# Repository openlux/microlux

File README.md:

This project is still in development.

# microlux

microlux is an open source design for an astrophotography autoguiding camera designed around the Aptina AR0130 image sensor.

### Hardware specifications

* AR0130 image sensor in ILCC48 package
  * 1280x960 resolution
  * 1/3-inch (6mm) diagonal size
  * 3.75um pixels
  * 78% peak quantum efficiency

* CY7C68013A microcontroller in QFN56 package
  * High speed USB 2.0 (480Mb/s)
  * Quad buffered 16/8 bit FIFO

* 40mm circular PCB
  * Designed to fit inside T2 / 42mm dust cap
  * 4x mounting holes for M2.5 screws (20mm square spacing)
  * Micro USB connector
  * RJ12 connector for ST4-compatible autoguiding

### PCB fab requirements

* Min. trace width 6mil
* Min. trace/pad spacing 6mil
* Min. drill 0.35mm
* Max. drill 2.7mm
* Min. via diameter 0.6mm
* Copper thickness 1.37mil (1oz/ft<sup>2</sup>)
* PCB thickness 0.8-1.6mm

### PCB photo

### PCB render

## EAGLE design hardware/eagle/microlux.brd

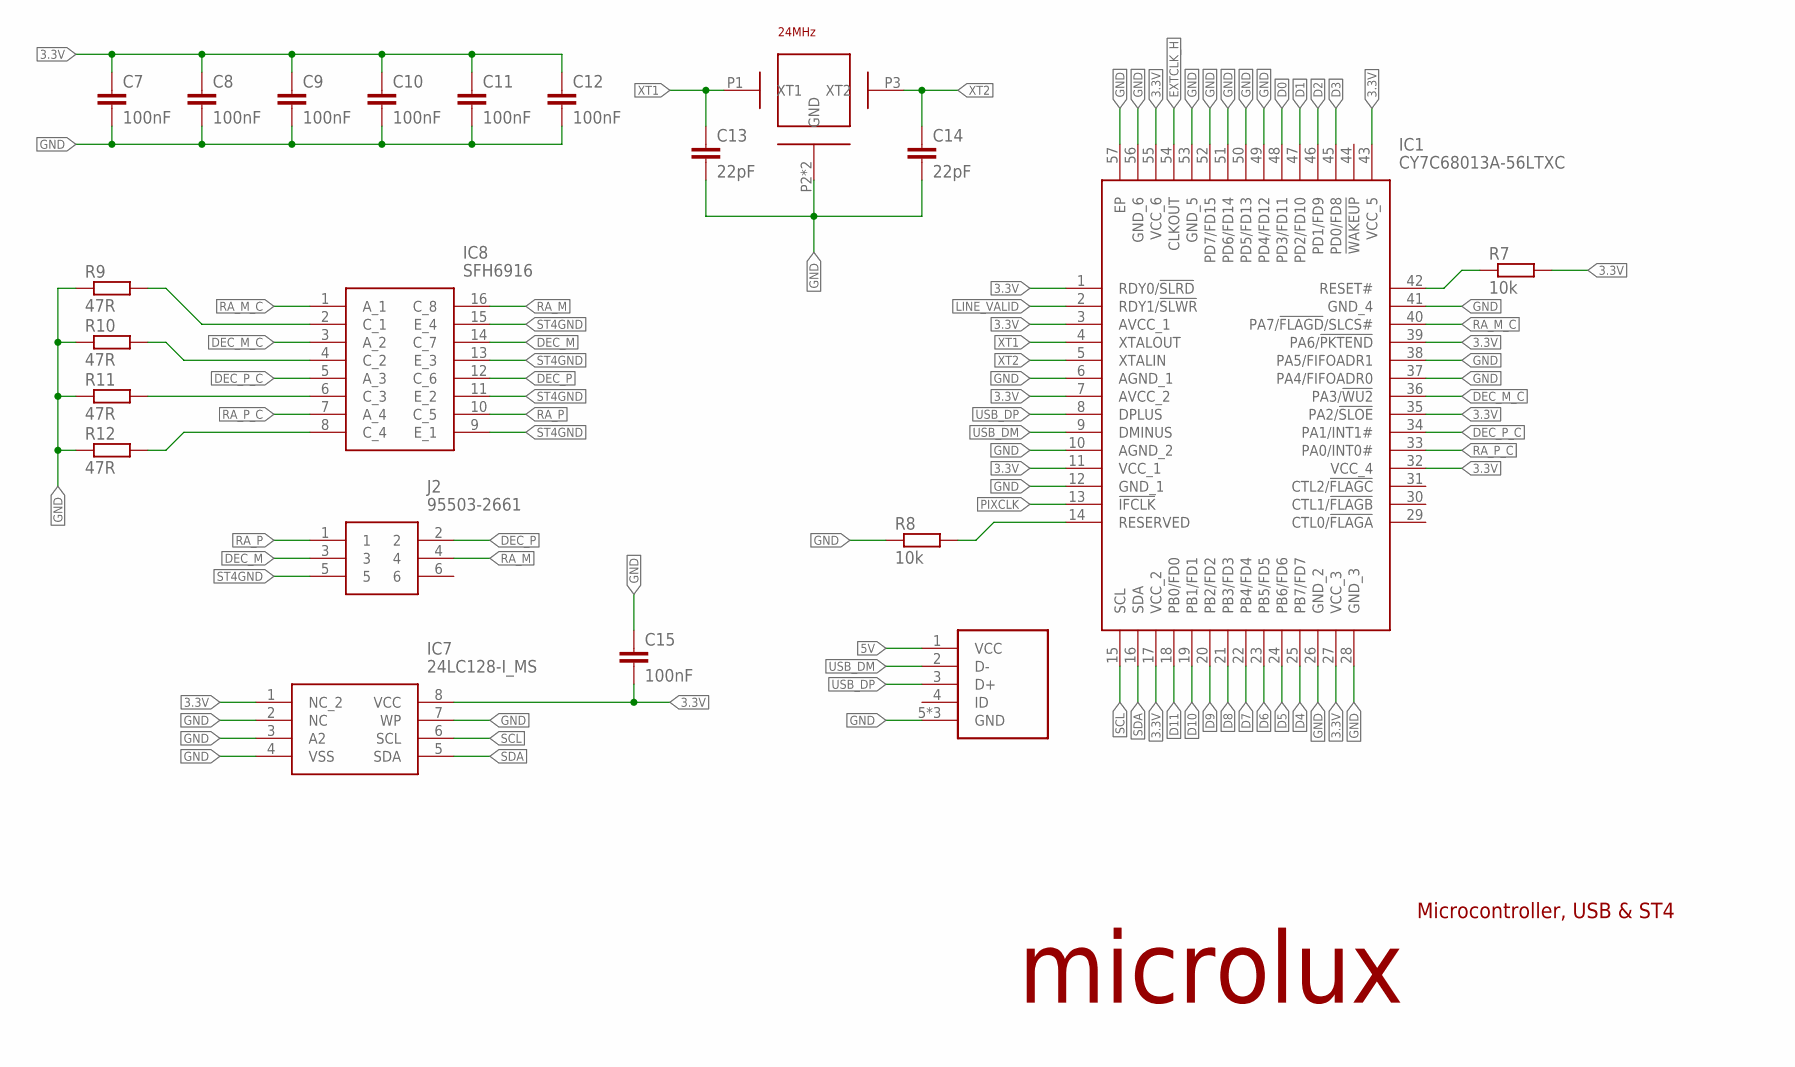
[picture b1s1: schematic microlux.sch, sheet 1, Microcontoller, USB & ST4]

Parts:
C7, C8, C9, C10, C11, C12, C15: 100nF; C0603
C13, C14: 22pF; C0603
IC1: CY7C68013A-56LTXC; QFN50P800X800X100-57N
IC7: 24LC128-I_MS; SOP65P490X110-8N
IC8: SFH6916; SOIC127P686X216-16N
J1: 614105150621; VMUSB
J2: 95503-2661; 955032661
R7, R8: 10k; R0603
R9, R10, R11, R12: 47R; R0603
X1: 24MHz; 3.2X2.5

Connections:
3.3V: C7.1, C8.1, C9.1, C10.1, C11.1, C12.1, C15.2, IC1.1 (RDY0/!SLRD), IC1.3 (AVCC_1), IC1.7 (AVCC_2), IC1.11 (VCC_1), IC1.17 (VCC_2), IC1.27 (VCC_3), IC1.32 (VCC_4), IC1.35 (PA2/!SLOE), IC1.39 (PA6/!PKTEND), IC1.43 (VCC_5), IC1.55 (VCC_6), IC7.1 (NC_2), IC7.8 (VCC), R7.2; also elsewhere on the board
5V: J1.1 (VCC); also elsewhere on the board
D0: IC1.48 (PD3/FD11); also elsewhere on the board
D1: IC1.47 (PD2/FD10); also elsewhere on the board
D2: IC1.46 (PD1/FD9); also elsewhere on the board
D3: IC1.45 (PD0/FD8); also elsewhere on the board
D4: IC1.25 (PB7/FD7); also elsewhere on the board
D5: IC1.24 (PB6/FD6); also elsewhere on the board
D6: IC1.23 (PB5/FD5); also elsewhere on the board
D7: IC1.22 (PB4/FD4); also elsewhere on the board
D8: IC1.21 (PB3/FD3); also elsewhere on the board
D9: IC1.20 (PB2/FD2); also elsewhere on the board
D10: IC1.19 (PB1/FD1); also elsewhere on the board
D11: IC1.18 (PB0/FD0); also elsewhere on the board
DEC_M: IC8.14 (C_7), J2.3
DEC_M_C: IC1.36 (PA3/!WU2), IC8.3 (A_2)
DEC_P: IC8.12 (C_6), J2.2
DEC_P_C: IC1.34 (PA1/INT1#), IC8.5 (A_3)
EXTCLK_H: IC1.54 (CLKOUT); also elsewhere on the board
GND: C7.2, C8.2, C9.2, C10.2, C11.2, C12.2, C13.2, C14.2, C15.1, IC1.6 (AGND_1), IC1.10 (AGND_2), IC1.12 (GND_1), IC1.26 (GND_2), IC1.28 (GND_3), IC1.37 (PA4/FIFOADR0), IC1.38 (PA5/FIFOADR1), IC1.41 (GND_4), IC1.49 (PD4/FD12), IC1.50 (PD5/FD13), IC1.51 (PD6/FD14), IC1.52 (PD7/FD15), IC1.53 (GND_5), IC1.56 (GND_6), IC1.57 (EP), IC7.2 (NC), IC7.3 (A2), IC7.4 (VSS), IC7.7 (WP), J1.5 (GND), J1.M1 (GND), J1.M2 (GND), R8.1, R9.1, R10.1, R11.1, R12.1, X1.P2 (GND), X1.P4 (GND); also elsewhere on the board
LINE_VALID: IC1.2 (RDY1/!SLWR); also elsewhere on the board
unnamed: IC1.14 (RESERVED), R8.2
unnamed: IC8.2 (C_1), R9.2
unnamed: IC1.42 (RESET#), R7.1
unnamed: IC8.4 (C_2), R10.2
unnamed: IC8.6 (C_3), R11.2
unnamed: IC8.8 (C_4), R12.2
PIXCLK: IC1.13 (!IFCLK); also elsewhere on the board
RA_M: IC8.16 (C_8), J2.4
RA_M_C: IC1.40 (PA7/!FLAGD!/SLCS#), IC8.1 (A_1)
RA_P: IC8.10 (C_5), J2.1
RA_P_C: IC1.33 (PA0/INT0#), IC8.7 (A_4)
SCL: IC1.15 (SCL), IC7.6 (SCL); also elsewhere on the board
SDA: IC1.16 (SDA), IC7.5 (SDA); also elsewhere on the board
ST4GND: IC8.9 (E_1), IC8.11 (E_2), IC8.13 (E_3), IC8.15 (E_4), J2.5
USB_DM: IC1.9 (DMINUS), J1.2 (D-)
USB_DP: IC1.8 (DPLUS), J1.3 (D+)
XT1: C13.1, IC1.4 (XTALOUT), X1.P1 (XT1)
XT2: C14.1, IC1.5 (XTALIN), X1.P3 (XT2)

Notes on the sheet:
microlux
Microcontroller, USB & ST4

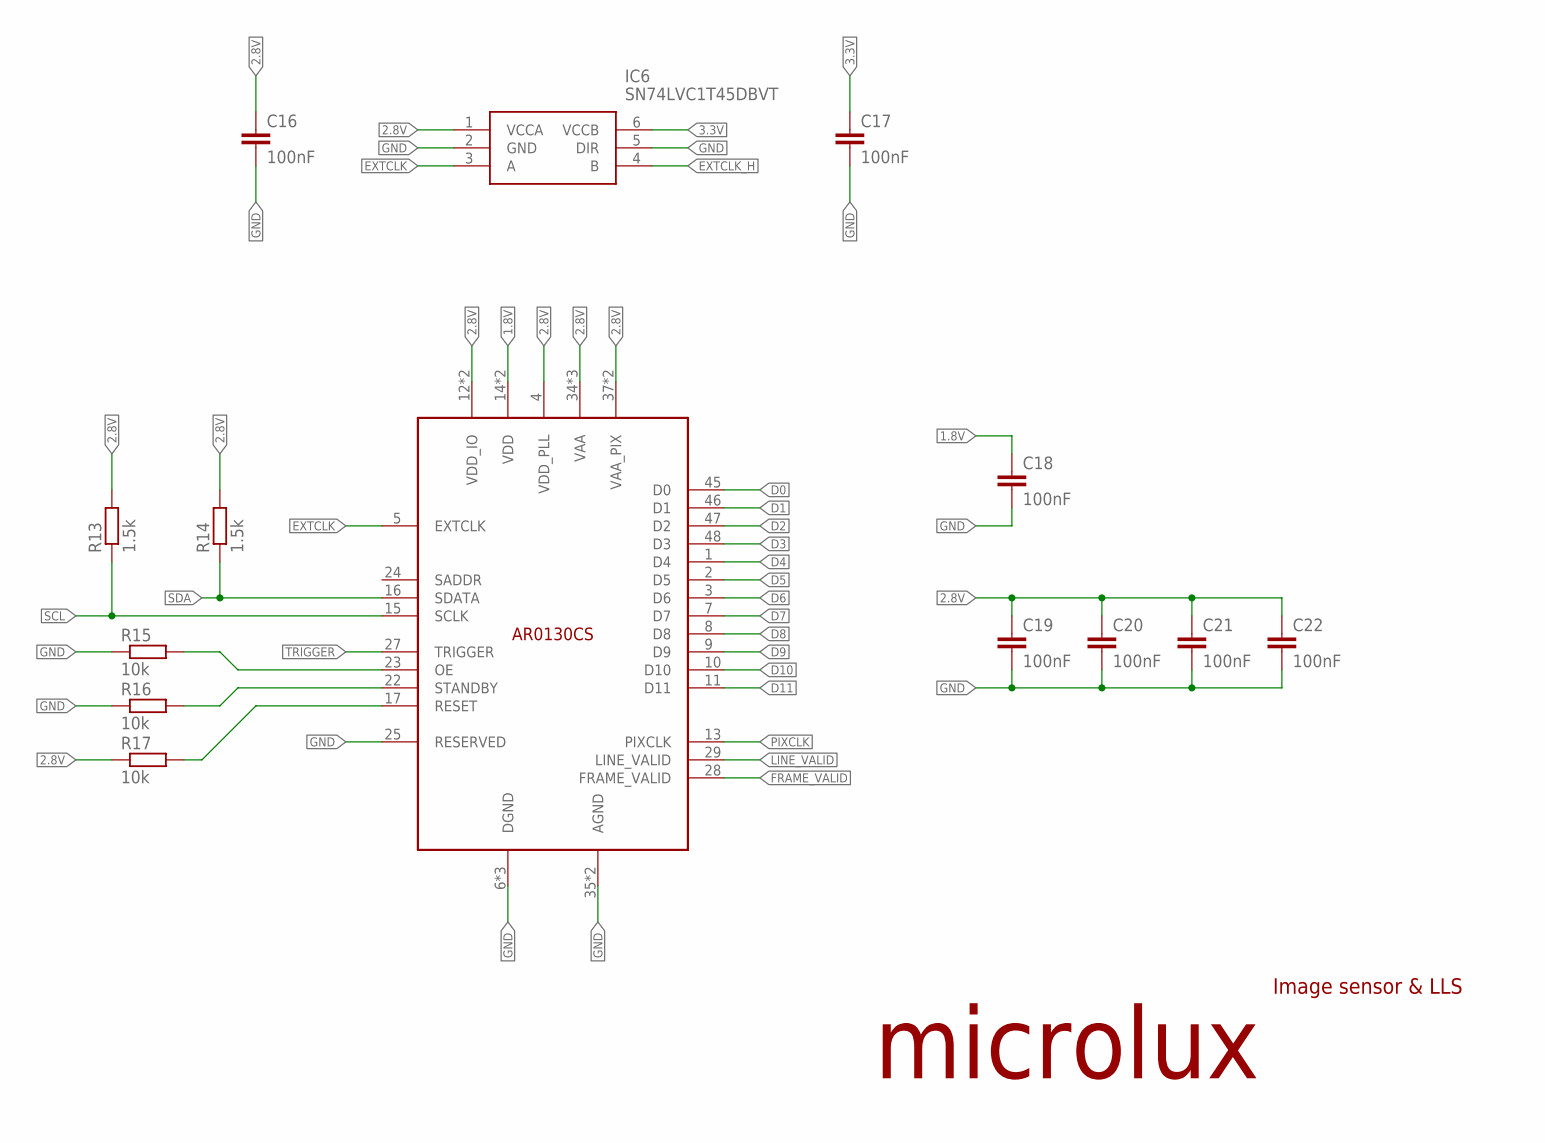
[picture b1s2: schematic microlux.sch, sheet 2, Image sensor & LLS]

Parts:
C16, C17, C18, C19, C20, C21, C22: 100nF; C0603
IC2: AR0130CS-ILCC48; ILCC48
IC6: SN74LVC1T45DBVT; SOT95P280X145-6N
R13, R14: 1.5k; R0603
R15, R16, R17: 10k; R0603

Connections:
1.8V: C18.1, IC2.14 (VDD), IC2.19 (VDD); also elsewhere on the board
2.8V: C16.1, C19.1, C20.1, C21.1, C22.1, IC2.4 (VDD_PLL), IC2.12 (VDD_IO), IC2.18 (VDD_IO), IC2.34 (VAA), IC2.36 (VAA), IC2.37 (VAA_PIX), IC2.38 (VAA_PIX), IC2.40 (VAA), IC6.1 (VCCA), R13.2, R14.2, R17.1; also elsewhere on the board
3.3V: C17.1, IC6.6 (VCCB); also elsewhere on the board
D0: IC2.45 (D0); also elsewhere on the board
D1: IC2.46 (D1); also elsewhere on the board
D2: IC2.47 (D2); also elsewhere on the board
D3: IC2.48 (D3); also elsewhere on the board
D4: IC2.1 (D4); also elsewhere on the board
D5: IC2.2 (D5); also elsewhere on the board
D6: IC2.3 (D6); also elsewhere on the board
D7: IC2.7 (D7); also elsewhere on the board
D8: IC2.8 (D8); also elsewhere on the board
D9: IC2.9 (D9); also elsewhere on the board
D10: IC2.10 (D10); also elsewhere on the board
D11: IC2.11 (D11); also elsewhere on the board
EXTCLK: IC2.5 (EXTCLK), IC6.3 (A)
EXTCLK_H: IC6.4 (B); also elsewhere on the board
FRAME_VALID: IC2.28 (FRAME_VALID)
GND: C16.2, C17.2, C18.2, C19.2, C20.2, C21.2, C22.2, IC2.6 (DGND), IC2.25 (RESERVED), IC2.30 (DGND), IC2.35 (AGND), IC2.39 (AGND), IC2.44 (DGND), IC6.2 (GND), IC6.5 (DIR), R15.1, R16.1; also elsewhere on the board
LINE_VALID: IC2.29 (LINE_VALID); also elsewhere on the board
unnamed: IC2.23 (OE), R15.2
unnamed: IC2.22 (STANDBY), R16.2
unnamed: IC2.17 (RESET), R17.2
PIXCLK: IC2.13 (PIXCLK); also elsewhere on the board
SCL: IC2.15 (SCLK), R13.1; also elsewhere on the board
SDA: IC2.16 (SDATA), R14.1; also elsewhere on the board
TRIGGER: IC2.27 (TRIGGER)

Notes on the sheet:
microlux
Image sensor & LLS

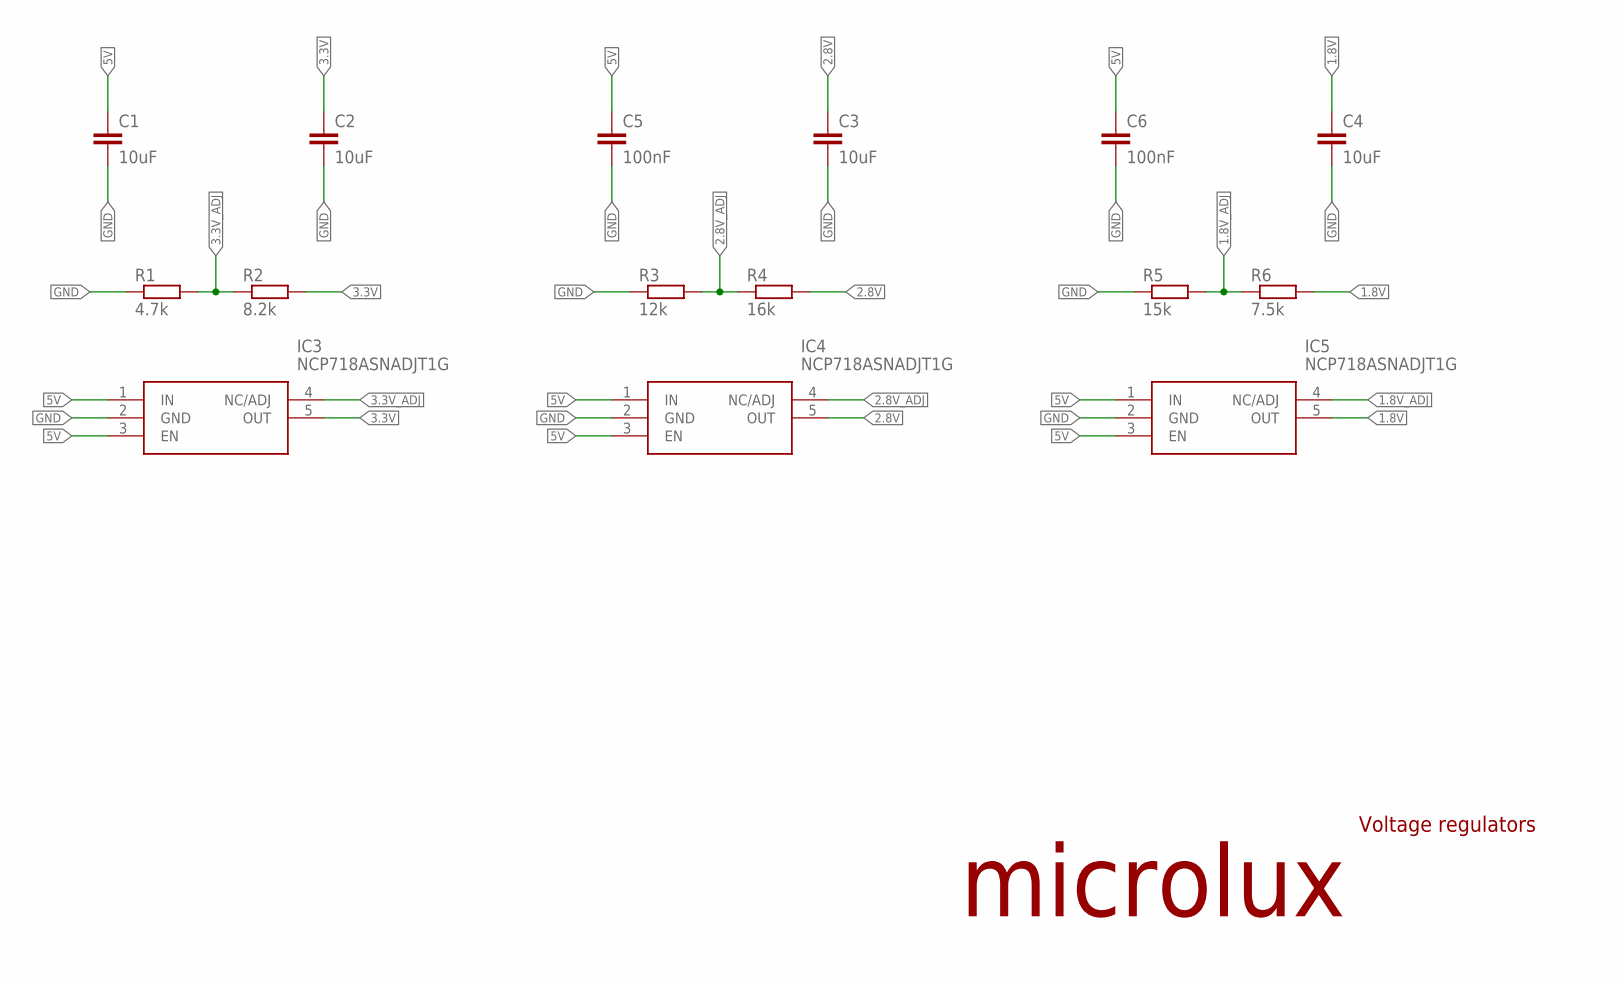
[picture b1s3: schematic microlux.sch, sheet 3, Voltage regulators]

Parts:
C1, C2, C3, C4: 10uF; C1210
C5, C6: 100nF; C0603
IC3, IC4, IC5: NCP718ASNADJT1G; SOT95P280X100-5N
R1: 4.7k; R0603
R2: 8.2k; R0603
R3: 12k; R0603
R4: 16k; R0603
R5: 15k; R0603
R6: 7.5k; R0603

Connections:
1.8V: C4.1, IC5.5 (OUT), R6.2; also elsewhere on the board
1.8V_ADJ: IC5.4 (NC/ADJ), R5.2, R6.1
2.8V: C3.1, IC4.5 (OUT), R4.2; also elsewhere on the board
2.8V_ADJ: IC4.4 (NC/ADJ), R3.2, R4.1
3.3V: C2.1, IC3.5 (OUT), R2.2; also elsewhere on the board
3.3V_ADJ: IC3.4 (NC/ADJ), R1.2, R2.1
5V: C1.1, C5.1, C6.1, IC3.1 (IN), IC3.3 (EN), IC4.1 (IN), IC4.3 (EN), IC5.1 (IN), IC5.3 (EN); also elsewhere on the board
GND: C1.2, C2.2, C3.2, C4.2, C5.2, C6.2, IC3.2 (GND), IC4.2 (GND), IC5.2 (GND), R1.1, R3.1, R5.1; also elsewhere on the board

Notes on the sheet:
microlux
Voltage regulators

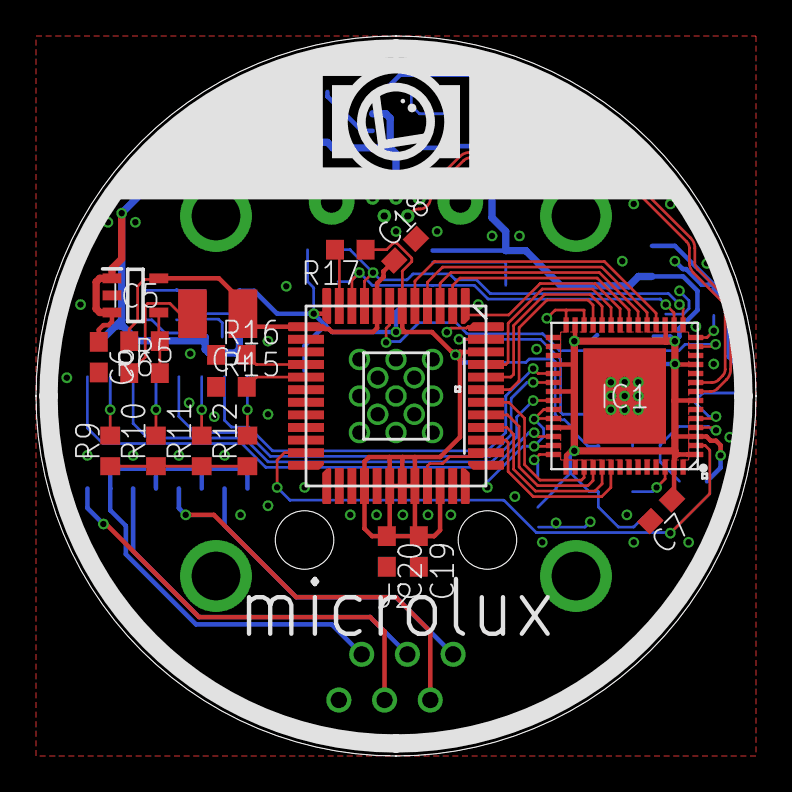
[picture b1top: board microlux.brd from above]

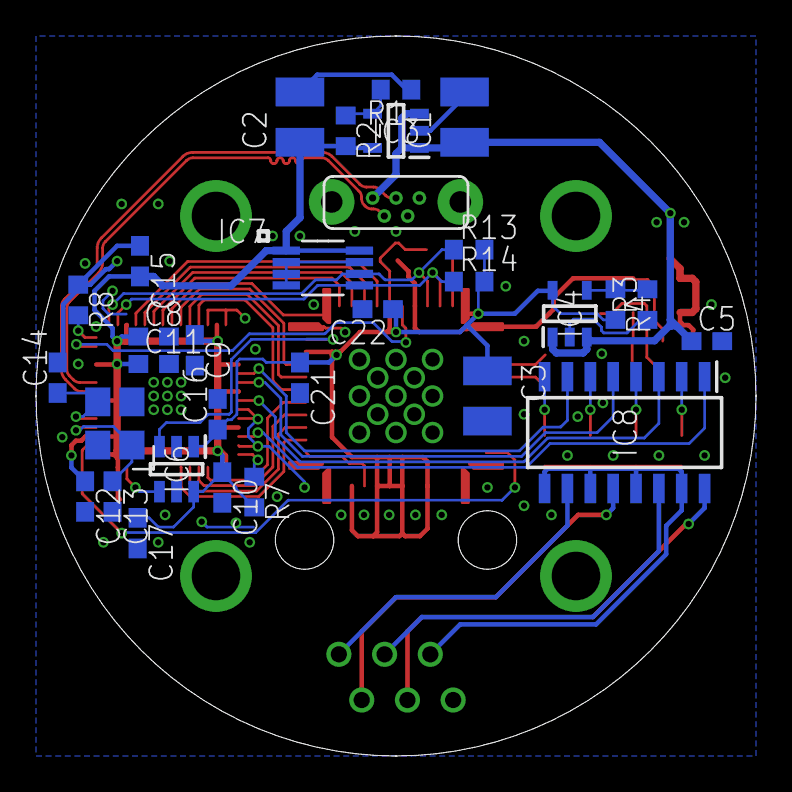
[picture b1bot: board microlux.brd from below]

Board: 2 copper layers, 40.0 x 40.0 mm, 50 parts (31 on the bottom side), 48 nets.

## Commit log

2019-01-04 Add manufacturer/product strings
2019-01-04 Set version to 1.00
2019-01-04 Add CDC-ACM descriptor
2019-01-04 Add handle_{get,set}_interface implementations
2019-01-04 Configure endpoints
2019-01-04 Reset endpoints in handle_set_interface
2019-01-04 Change vendor and product ID
    If we use 04B4:8613 Linux selects the usbtest driver rather than
    cdc_acm, so it doesn't create a /dev/ttyACM0 device.
2019-01-04 Mark dosud as static
2019-01-04 Add comments to main
2019-01-04 Send 'hello, world' message to the host after configuration
2019-01-04 Add CDC vendor commands
2019-01-04 Empty EP2 buffer
2019-01-04 Fix unused argument warning in handle_reset_ep
2019-01-04 Split USB and USB-CDC code into separate files
2019-01-04 Expose usb_configured variable
2019-01-04 Add utioa function
2019-01-04 Add initial I2C driver
2019-01-05 Use EP4/8 for CDC instead of EP2/6
    I want to save EP2/6 for the slave FIFO, as they have quad buffering.
2019-01-05 Use types from std{bool,int}.h in usb.c
2019-01-05 Add AR0130CS register read and write functions
2019-01-05 Add vendor-specfic endpoint for the USB FIFO
2019-01-05 Add trigger pin support
2019-01-05 Enable REVCTL bits
2019-01-05 Add 'final' product ID
2019-01-05 Enable 48 MHz IFCLK before the external IFCLK
    All our SYNCDELAYS assume that the CPU clock and IFCLK are both 48 MHz
    all the time.
2019-01-05 Add AR0130 initialization code
    This seems to be the bare minimum to get PIXCLK running at 48 MHz ready
    for switching IFCLK to the external clock.
2019-01-05 Enable CLKOUT
2019-01-05 Reduce SYNCDELAY cycles
2019-01-05 Switch to external IFCLK after starting the AR0130 PIXCLK
2019-01-05 Reset all FIFOs after configuring the endpoints
    The examples from the datasheet do this.
2019-01-05 Add USB FIFO support
2019-01-05 Remove ar0130_trigger
    We have to enable streaming mode to ensure that PIXCLK runs all the
    time, so trigger support is pointless.
2019-01-06 Flush EP2 on FRAME_VALID falling edges
2019-01-28 Restructure
2019-01-28 Add hardware
2019-01-28 Add schematic pdf
2019-01-28 Reduce mcu clockspeed to 12mhz
2019-01-28 Remove unused interrupt
2019-01-28 Add readme & move gitignore
2019-01-28 Fix gitignore build path etc
2019-02-01 Add fx2lib as submodule
2019-02-01 Add serial number string to descriptor
2019-02-01 Add license
2019-02-02 Correct mistake in license author
2019-02-02 Fix capitalization on license/readme
2019-02-02 Fix LSB of setup data pointer in CDC_GET_LINE_CODING
2019-02-08 Fix arming EP0 for an OUT transfer in CDC_SET_LINE_CODING
2019-02-13 Add vendor command for exposure configuration
2019-02-13 Add visual studio files to .gitignore
2019-02-13 Add initial ASCOM driver
2019-02-13 Add gerber files to .gitignore
2019-02-13 Change constant naming
2019-02-13 Replace compare_config with memcmp
2019-02-13 Remove blank line from the end of ar0130.c
2019-02-13 Make start_exposure static
    It doesn't need to be exposed publicly.
2019-02-13 Move camera_handle_command below ar0130_init for consistency
2019-02-13 Add ar0130_ prefix to functions, variables, structs and constants
2019-02-13 Remove unused AR0130_SET_REGISTER constant
2019-02-13 Sort includes in usb.c
2019-02-13 Replace SETUPDAT[0] with SETUP_TYPE
2019-02-13 Remove SETUP_TYPE check in handle_vendorcommand
    handle_vendorcommand returns a boolean so that we don't need to check
    any of the SETUP packet values in the top-level function.
2019-02-13 Move ar0130_exposure_config struct to ar0130.c
    It isn't used by any of the declarations in the header file.
2019-02-13 Remove unused commented code
2019-02-13 Add comment clarifying why we can use memcmp()
2019-02-13 Remove unused usb_fifo_flush() function
2019-02-13 Update comment in ar0130_init()
2019-02-13 Disable zero-length packets
    At one point I was thinking about using them for frame synchronization,
    but this is now done by looking for the frame's synchronization marker.
2019-02-13 Decouple AR0130 driver from the USB code
2019-02-13 Remove unused includes from ar0130.c
2019-02-13 Use switch in usb_ar0130_handle_command
    This is consistent with usb_cdc_handle_command.
2019-02-13 Rename constants & remove unused variable
2019-02-13 Change offset to constant
2019-02-13 Add stop exposure support and disable frame streaming by default
2019-02-13 Allow aborting exposure
2019-02-13 Set image ready to false after stopping exposure
2019-03-12 Add rename target to makefile
2019-03-12 Change rename target to copy
2019-03-12 Add executable files to gitignore
2019-03-12 Add innosetup installer script
2019-03-12 Rework copy target
2019-03-12 Add hardware specs + images to readme
2019-03-12 Reword pcb fab reqs in readme
2019-03-13 Add firmware support for aborting exposures
2019-03-13 Only abort exposures longer than 250ms
2019-03-13 Fix exposure threshold to use current duration not new duration
2019-03-13 Add zebra lines to readout and decrease buffer size to reduce frame latency
